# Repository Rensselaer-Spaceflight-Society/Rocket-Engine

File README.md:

# RPU Systems Design and Communications Protocol V1.1.0

> [!IMPORTANT]
> Last Updated: 9/22/2024

Below is a brief overview of the design and communications protocol between our laptop acting as our remote interface (i.e. the control room) and the Rocket Engine Test Stand itself.

## Table of Contents

- [Control Room](#control-room)
- [Test Stand Controller](#test-stand-controller)
- [Powering the Test Stand](#powering-the-test-stand)
- [Sensors](#sensors)
- [Valves](#valves)
- [Communications](#communications)
- [Command and Control](#command-and-control)
- [Sensor Data Transfer](#sensor-data-transfer)
- [Control Flow](#control-flow)
- [Arduino Pinout](#arduino-pinout)
- [Additional Info](#additional-info)

## Control Room

The software that remotely monitors the engine and allows us to send commands to the engine. This software is responsible for:

- Countdown
- Receiving and Saving Data
- Hold and Abort Signals
- Displaying the Data in a Human Friendly Way
  - Charts
  - Text Outputs
  - Color coding for if data is out of spec

### Technologies

We are using C++ and Qt 6.7.2 to build the control room software. You can install the Qt framework for Open Source Usage from https://www.qt.io/download-open-source.

## Test Stand Controller

The rocket engine controller is an Arduino based platform that controls the physical aspects of the rocket engine. This was the primary focus for the semester and is still the primary focus for this summer. This software is responsible for:

- Reading Sensors
- Opening and Closing Valves
- Sending Sensor Data back to the Control Room
- Ignition and Shutoff Sequence
- Processing Control Signals

## Powering the Test Stand

We have a variety of electronics that need power:

- Solenoid Valves, 48W (12vdc @4A)
- Arduino, 1W (12vdc @0.08333)
- Sensors, 5W (5v @1A)

The sensors need 5v, but everything else needs 12v, fortunately, the Arduino's power regulation will step the power down to 5v for the sensors.

Its really hard to send 60w @ 12vdc over 300ft, so we decided that battery power is our best bet for powering the test stand. Lithium Iron Phosphate (LiFePO4) batteries show the best potential for delivering both the voltage and current that the test stand will need.

The use of battery power allows us to set our downrange distance anywhere from 300ft (100m) - 3400ft (1000m).

### Technologies

This is built on the Arduino platform for easy and plentiful I/O. Arduino provides plenty of digital and analog pins for reading sensors and controlling valves. It also provides simple serial communications over UART.

> [!NOTE]
> Originally the rocket engine was supposed to be controlled via Raspberry Pi, we switched to the arduino platform for a couple reasons.
>
> - Setup is easier as there is no need to ssh into the arduino and run the control program, it starts up automatically on power on.
> - The Raspberry Pi has no Analog pin headers, the pressure transducers are analog sensors, switching to Arduino removes the need for analog-digital converters.
> - The Arduino takes less power, we can power it really easily via the VIN and GND pins compared to RasPI which is much harder to power
> - Arduino has first class support for our serial communications, where as raspberry pi has support but is slightly more difficult to implement
> - Arduino has no OS that is also has to run, it just runs our code and our code only.

## Sensors

The rocket engine has 8 sensors:

- 1 Load Cell for measuring thrust
- 4 Thermocouples placed before the injector plate
    - Each one placed at on the injector plate next to the fuel inlets.
- 6 Pressure Transducers
  - 1 Inside the Combustion Chamber
    - According to David, the back of the combustion chamber should be cool enough to not destroy this sensor
  - 1 Down Line of the Inert Gas System
  - 2 Before the injector plate
    - 1 for fuel
    - 1 for oxidizer
  - 2 After the valves for fuel and oxidizer

The pressure transducers are analog sensors that vary their voltage depending on the pressure they are detecting.

The thermocouple and load cell both have amplifiers that act as analog-digital converters. The signals we take in will be digital signals. The thermocouple unfortunately does work on SPI (sorry Ashton).

## Valves

We are using three 12v solenoid valves that operate at 1.33 amps. This is simply too much power to send over a wire with our budget. See the power section for more information.

Power will be delivered to the solenoids via solid-state relays, this allows the
5v logic level of the Arduino power the relays reliably.

## Communications

The goal is to not be anywhere close to the engine when it is firing, the team is still deciding on an acceptable distance, but the current number is between 50 - 100m (170 - 340ft). To achieve this range with easy and reliable communications we are using UART serial communications via ethernet. This provides a well supported, and robust communication method.

> [!IMPORTANT]
> The Baud Rate for the serial communications has yet to be finalized, for testing we are using 9600 but this may change in the future.

Specifically the serial data will be converted to RS485 and sent over Cat 5 ethernet cable, this is supposedly an effective way to handle long range wired communication. [Source](https://electronics.stackexchange.com/questions/113188/long-distance-communication)

The Arduino's serial communication library automatically handles parity, start, and stop bits, so we don't need to handle this necessarily. The default is 8 data, 1 start and 1 stop bit with no parity, but we may be able to change this if needed.

Communications should be handled over the the Serial1 Port on the Arduino, Serial0 (aka just "Serial) is reserved for debugging via the Serial Monitor.

## Command and Control

The control room and the test stand use 64 bit (8 byte) signals to communicate different actions / states to each other the signals are as follows. When the test stand receives a command it should send an acknowledgement. If the control room fails to receive an acknowledgement it should reattempt sending the command up to **5** times. If after these
attempts there still is no acknowledgement, then the control room should assume connection
is lost and notify the user. If the test stand receives a command that it has already received then it should just send an acknowledgement instead of rerunning code.

We are still deciding on what the test stand should do if connection is lost. This document will be updated when this is decided.

The countdown is activated by clicking on the "Start Countdown" button, which will start the countdown from 5 minutes. Once the countdown gets to 30 second, the countdown pauses until you click on the same button that will now read "Resume Countdown". Once you click on it and the countdown reaches 0, it emits a countdown to the main thread where we will begin communication with the rocket. If you click on "Stop Countdown" at any point, the timer will stop at that specific time. Clicking on "Start Countdown" will restart from 5 minutes.

The acknowledgement is an 8 byte sequence:
`Accepted`

The following sequences are the different commands sent by the control computer and what
they tell the test stand to do.

- `CtrlActi` Control Computer Active, tells the test stand that a communication link is active.
- `LogStart` Tells the test stand to start the logging of sensor data and communicating that down the line.
- `InrtFlsh` Tells the test stand to perform an inert gas flush
- `PresFuel` Tells the test stand to open the pressure valve to the Kerosene
- `Ignition` Tells the test stand to open the valves and light the Steel Wool following the ignition protocol
- `Shutdown` Tells the test stand to close the oxidizer valve first, then the fuel valve.

On Shutdown, the test stand should send a message that the engine was shutdown.

## Sensor Data Transfer

Sensor data is sent in packets of 44 bytes of binary data with the following structure:

```cpp
typedef struct
{
  float loadCell;
  float thermocouple[4];
  float pressure[6];
} SensorData;
```

## Control Flow

1. The test stand and the control computer will come online, the control computer will start sending out the signal `CtrlActi` signal. When the test stand receives this, it will send the acknowledgement. On receiving the acknowledgement, the control stand will recognize a connection being solid.
2. The control computer will send the `LogStart` command to tell the test stand to start logging, the test stands sends the acknowledgement, and then will start sending sensor data.
3. At T-10s We will send the `InrtFlsh` command to trigger the test-stand to do the inert flush. 
4. At T-5s We will send the `PresFuel` command to trigger the opening of fuel pressurization valve
5. At T-0.5s We will send the `Ignition` command to initiate the ignition sequence
6. If the test stand detects an anomaly / the end of the test, then it will shutdown and send a message that it shutdown.
7. If the test stand receives the `Shutdown` message, then it should run the shutdown procedure and alert that it shutdown.

## Arduino Pinout

See the Schematic using KiCad for the most up to date Arduino Pins.

## Additional Info

For additional info into how to build the Control Room software, configure the Arduino, and other parts of the project, consult the docs folder of the [GitHub Repository](https://github.com/Rensselaer-Spaceflight-Society/Rocket-Engine)

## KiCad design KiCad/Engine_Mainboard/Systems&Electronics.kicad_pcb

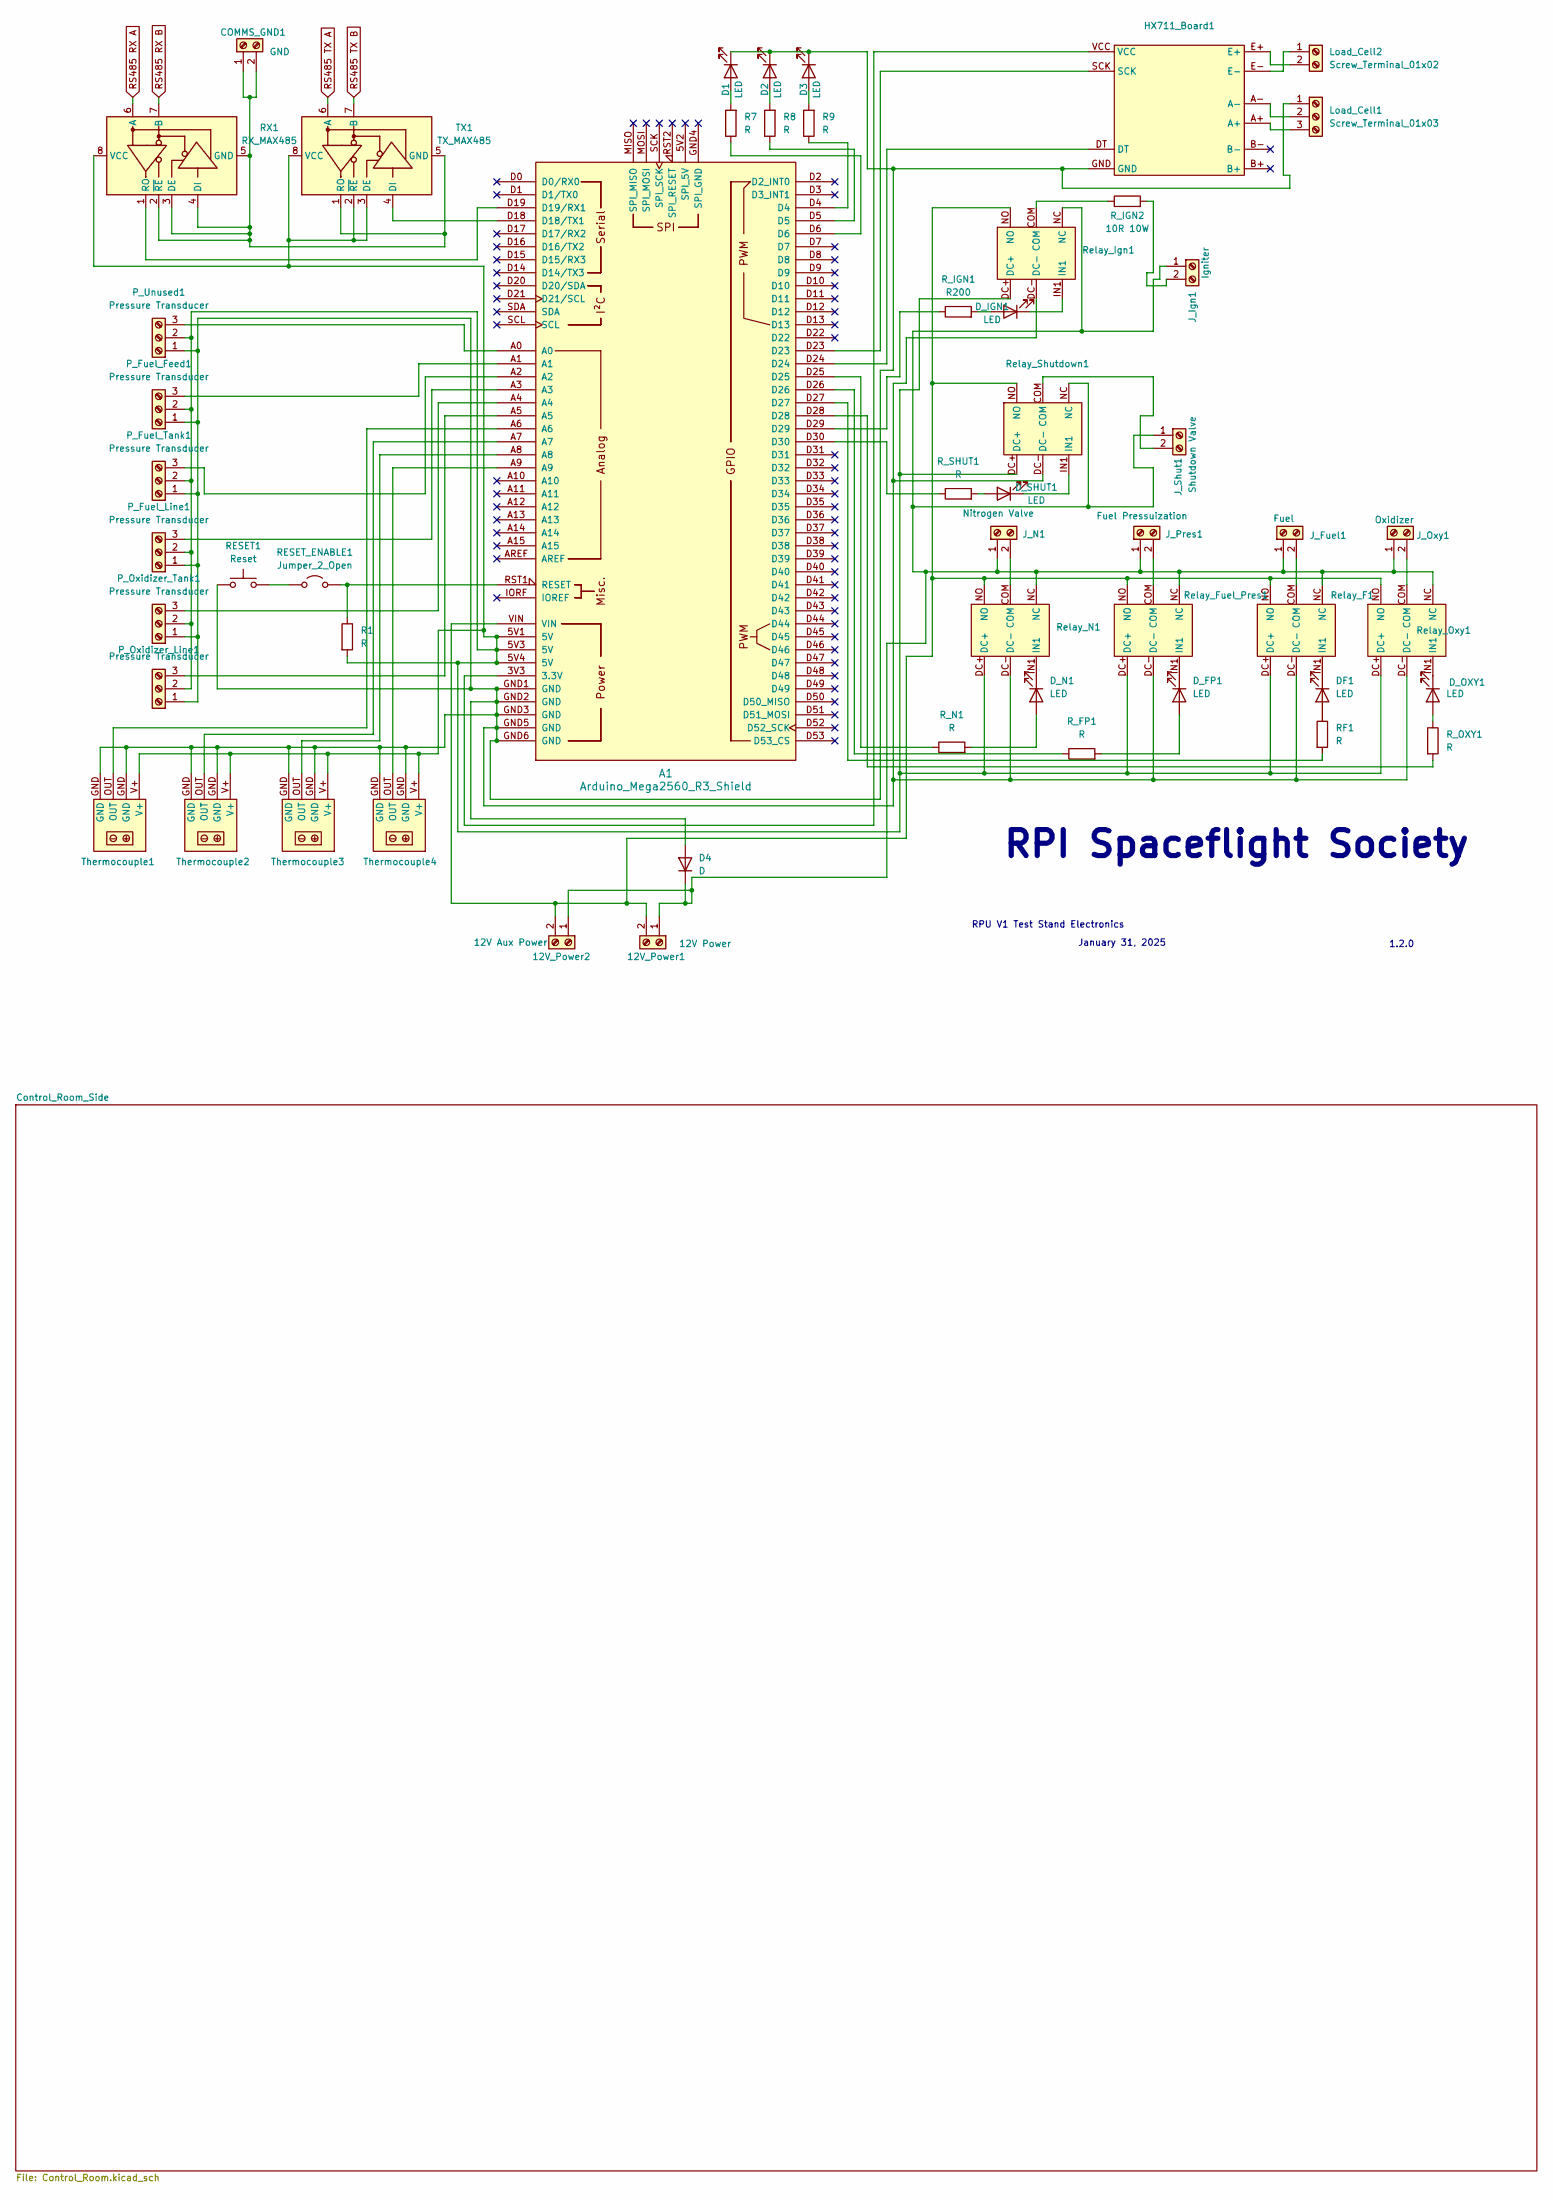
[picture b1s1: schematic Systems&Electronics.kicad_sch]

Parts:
12V_Power1: 12V Power; TerminalBlock_bornier-2_P5.08mm
12V_Power2: 12V Aux Power; TerminalBlock_bornier-2_P5.08mm
A1: Arduino_Mega2560_R3_Shield
COMMS_GND1: GND; TerminalBlock_bornier-2_P5.08mm
D1, D2, D3: LED; LED_D5.0mm
D4: D; D_A-405_P7.62mm_Horizontal
DF1: LED; LED_D5.0mm
D_FP1: LED; LED_D5.0mm
D_IGN1: LED; LED_D5.0mm
D_N1: LED; LED_D5.0mm
D_OXY1: LED; LED_D5.0mm
D_SHUT1: LED; LED_D5.0mm
HX711_Board1: HX711
J_Fuel1: Fuel; TerminalBlock_bornier-2_P5.08mm
J_Ign1: Igniter; TerminalBlock_bornier-2_P5.08mm
J_N1: Nitrogen Valve; TerminalBlock_bornier-2_P5.08mm
J_Oxy1: Oxidizer; TerminalBlock_bornier-2_P5.08mm
J_Pres1: Fuel Pressuization; TerminalBlock_bornier-2_P5.08mm
J_Shut1: Shutdown Valve; TerminalBlock_bornier-2_P5.08mm
Load_Cell1: Screw_Terminal_01x03; TerminalBlock_bornier-3_P5.08mm
Load_Cell2: Screw_Terminal_01x02; TerminalBlock_bornier-2_P5.08mm
P_Fuel_Feed1: Pressure Transducer; TerminalBlock_bornier-3_P5.08mm
P_Fuel_Line1: Pressure Transducer; TerminalBlock_bornier-3_P5.08mm
P_Fuel_Tank1: Pressure Transducer; TerminalBlock_bornier-3_P5.08mm
P_Oxidizer_Line1: Pressure Transducer; TerminalBlock_bornier-3_P5.08mm
P_Oxidizer_Tank1: Pressure Transducer; TerminalBlock_bornier-3_P5.08mm
P_Unused1: Pressure Transducer; TerminalBlock_bornier-3_P5.08mm
R1, R7, R8, R9: R; R_Axial_DIN0207_L6.3mm_D2.5mm_P7.62mm_Horizontal
RESET1: Reset; SW_PUSH_6mm
RESET_ENABLE1: Jumper_2_Open; PinHeader_1x02_P2.54mm_Vertical
RF1: R; R_Axial_DIN0207_L6.3mm_D2.5mm_P7.62mm_Horizontal
RX1: RX_MAX485; RS485_Transceiver
R_FP1: R; R_Axial_DIN0207_L6.3mm_D2.5mm_P7.62mm_Horizontal
R_IGN1: R200; R_Axial_DIN0207_L6.3mm_D2.5mm_P7.62mm_Horizontal
R_IGN2: 10R 10W; R_Axial_Power_L50.0mm_W9.0mm_P55.88mm
R_N1: R; R_Axial_DIN0207_L6.3mm_D2.5mm_P7.62mm_Horizontal
R_OXY1: R; R_Axial_DIN0207_L6.3mm_D2.5mm_P7.62mm_Horizontal
R_SHUT1: R; R_Axial_DIN0207_L6.3mm_D2.5mm_P7.62mm_Horizontal
Relay_F1: Relay
Relay_Fuel_Pres1: Relay
Relay_Ign1: Relay
Relay_N1: Relay
Relay_Oxy1: Relay
Relay_Shutdown1: Relay
TX1: TX_MAX485; RS485_Transceiver
Thermocouple1, Thermocouple2, Thermocouple3, Thermocouple4: AD8495

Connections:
unnamed: 12V_Power1.1, 12V_Power2.1, D4.1 (K), J_Fuel1.1, J_Ign1.1, J_N1.1, J_Oxy1.1, J_Pres1.1, J_Shut1.1, Relay_F1.NC, Relay_Fuel_Pres1.NC, Relay_Ign1.NC, Relay_N1.NC, Relay_Oxy1.NC, Relay_Shutdown1.NC
unnamed: 12V_Power1.2, 12V_Power2.2, A1.VIN, Relay_F1.NO, Relay_Fuel_Pres1.NO, Relay_Ign1.NO, Relay_N1.NO, Relay_Oxy1.NO, Relay_Shutdown1.NO
unnamed: A1.3V3 (3.3V), HX711_Board1.VCC
unnamed: A1.D18 (D18/TX1), TX1.4 (DI)
unnamed: A1.D19 (D19/RX1), RX1.1 (RO)
unnamed: A1.A6, Thermocouple1.OUT
unnamed: A1.A7, Thermocouple2.OUT
unnamed: A1.A8, Thermocouple3.OUT
unnamed: A1.A9, Thermocouple4.OUT
unnamed: A1.D4, R9.1
unnamed: A1.D5, R8.1
unnamed: A1.D6, R7.1
unnamed: A1.D23, HX711_Board1.SCK
unnamed: A1.D24, HX711_Board1.DT
unnamed: A1.D25, R_N1.1
unnamed: A1.D26, R_FP1.1
unnamed: A1.D27, RF1.2
unnamed: A1.D28, R_OXY1.2
unnamed: A1.D29, R_IGN1.1
unnamed: A1.D30, R_SHUT1.1
unnamed: A1.RST1 (RESET), R1.1, RESET_ENABLE1.2 (B)
unnamed: COMMS_GND1.1, COMMS_GND1.2, RX1.2 (~RE), RX1.3 (DE), RX1.4 (DI), RX1.5 (GND), TX1.1 (RO), TX1.5 (GND)
unnamed: D1.2 (A), R7.2
unnamed: A1.GND1 (GND), A1.GND2 (GND), A1.GND3 (GND), A1.GND5 (GND), A1.GND6 (GND), D1.1 (K), D2.1 (K), D3.1 (K), D4.2 (A), HX711_Board1.GND, Load_Cell1.1, P_Fuel_Feed1.1, P_Fuel_Line1.1, P_Fuel_Tank1.1, P_Oxidizer_Line1.1, P_Oxidizer_Tank1.1, P_Unused1.1, RESET1.1, Relay_F1.DC-, Relay_Fuel_Pres1.DC-, Relay_Ign1.DC-, Relay_N1.DC-, Relay_Oxy1.DC-, Relay_Shutdown1.DC-, Thermocouple1.GND, Thermocouple2.GND, Thermocouple3.GND, Thermocouple4.GND
unnamed: D2.2 (A), R8.2
unnamed: D3.2 (A), R9.2
unnamed: DF1.2 (A), RF1.1
unnamed: DF1.1 (K), Relay_F1.IN1
unnamed: D_FP1.2 (A), R_FP1.2
unnamed: D_FP1.1 (K), Relay_Fuel_Pres1.IN1
unnamed: D_IGN1.2 (A), R_IGN1.2
unnamed: D_IGN1.1 (K), Relay_Ign1.IN1
unnamed: D_N1.2 (A), R_N1.2
unnamed: D_N1.1 (K), Relay_N1.IN1
unnamed: D_OXY1.2 (A), R_OXY1.1
unnamed: D_OXY1.1 (K), Relay_Oxy1.IN1
unnamed: D_SHUT1.2 (A), R_SHUT1.2
unnamed: D_SHUT1.1 (K), Relay_Shutdown1.IN1
unnamed: J_Fuel1.2, Relay_F1.COM
unnamed: J_Ign1.2, R_IGN2.2
unnamed: J_N1.2, Relay_N1.COM
unnamed: J_Oxy1.2, Relay_Oxy1.COM
unnamed: J_Pres1.2, Relay_Fuel_Pres1.COM
unnamed: J_Shut1.2, Relay_Shutdown1.COM
unnamed: HX711_Board1.A-, Load_Cell1.2
unnamed: HX711_Board1.A+, Load_Cell1.3
unnamed: HX711_Board1.E-, Load_Cell2.1
unnamed: HX711_Board1.E+, Load_Cell2.2
unnamed: A1.5V1 (5V), A1.5V3 (5V), A1.5V4 (5V), P_Fuel_Feed1.2, P_Fuel_Line1.2, P_Fuel_Tank1.2, P_Oxidizer_Line1.2, P_Oxidizer_Tank1.2, P_Unused1.2, R1.2, RX1.8 (VCC), Relay_F1.DC+, Relay_Fuel_Pres1.DC+, Relay_Ign1.DC+, Relay_N1.DC+, Relay_Oxy1.DC+, Relay_Shutdown1.DC+, TX1.2 (~RE), TX1.3 (DE), TX1.8 (VCC), Thermocouple1.V+, Thermocouple2.V+, Thermocouple3.V+, Thermocouple4.V+
unnamed: A1.A1, P_Fuel_Feed1.3
unnamed: A1.A3, P_Fuel_Line1.3
unnamed: A1.A2, P_Fuel_Tank1.3
unnamed: A1.A5, P_Oxidizer_Line1.3
unnamed: A1.A4, P_Oxidizer_Tank1.3
unnamed: A1.A0, P_Unused1.3
unnamed: RESET1.2, RESET_ENABLE1.1 (A)
unnamed: R_IGN2.1, Relay_Ign1.COM
RS485 RX A: RX1.6 (A)
RS485 RX B: RX1.7 (B)
RS485 TX A: TX1.6 (A)
RS485 TX B: TX1.7 (B)

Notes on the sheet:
RPU V1 Test Stand Electronics
RPI Spaceflight Society
January 31, 2025
1.2.0

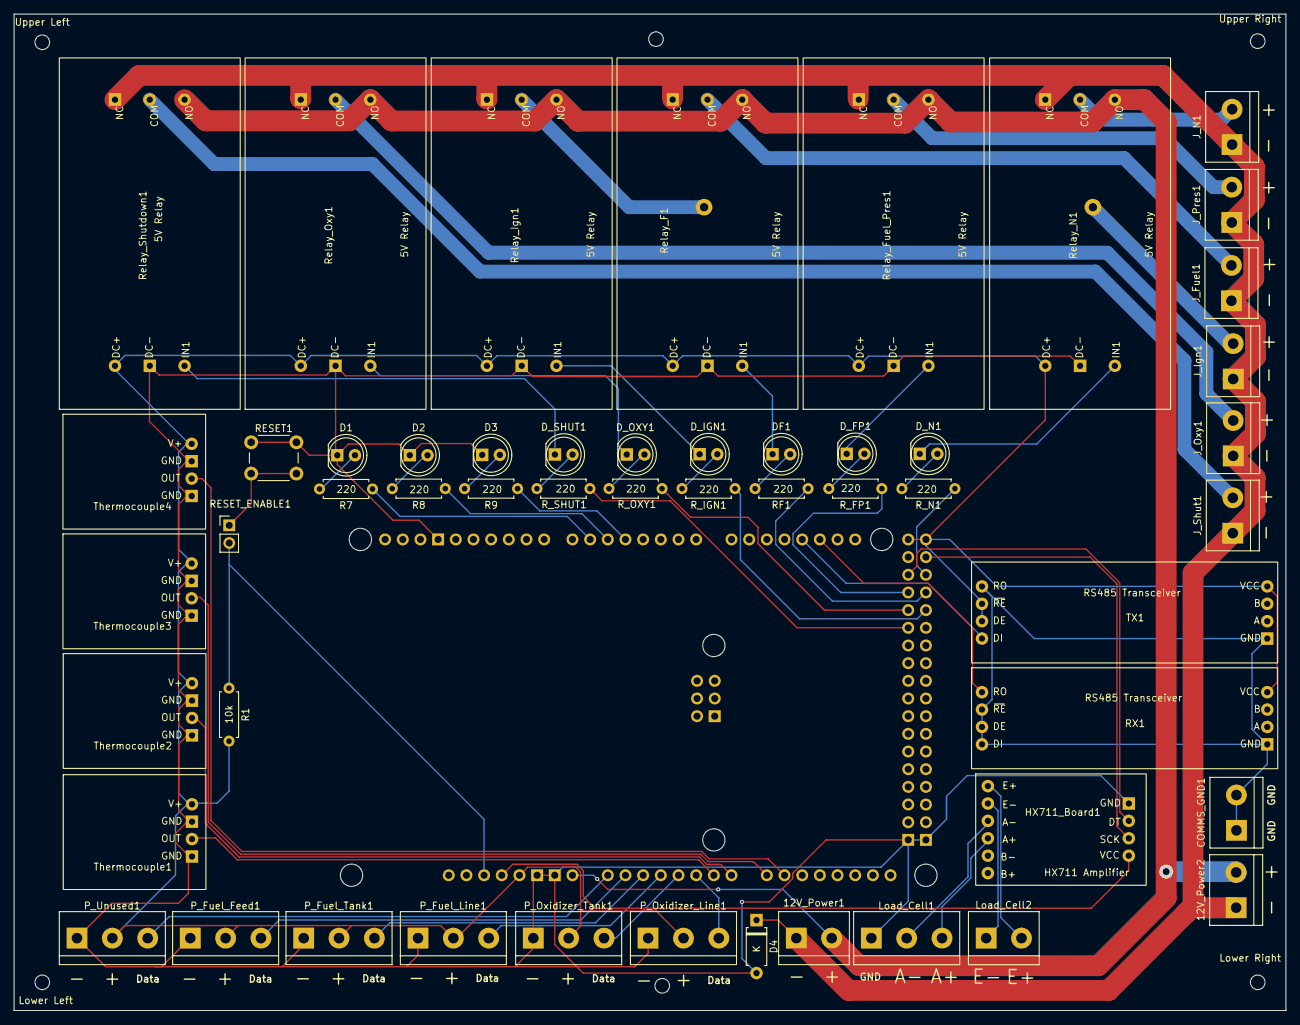
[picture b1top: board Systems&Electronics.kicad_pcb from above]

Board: 2 copper layers, 182.8 x 143.2 mm, 58 parts (1 on the bottom side), 57 nets.

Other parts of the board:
Lower Left: MountingHole_2.1mm
Lower Right: MountingHole_2.1mm
Upper Left: MountingHole_2.1mm
Upper Right: MountingHole_2.1mm

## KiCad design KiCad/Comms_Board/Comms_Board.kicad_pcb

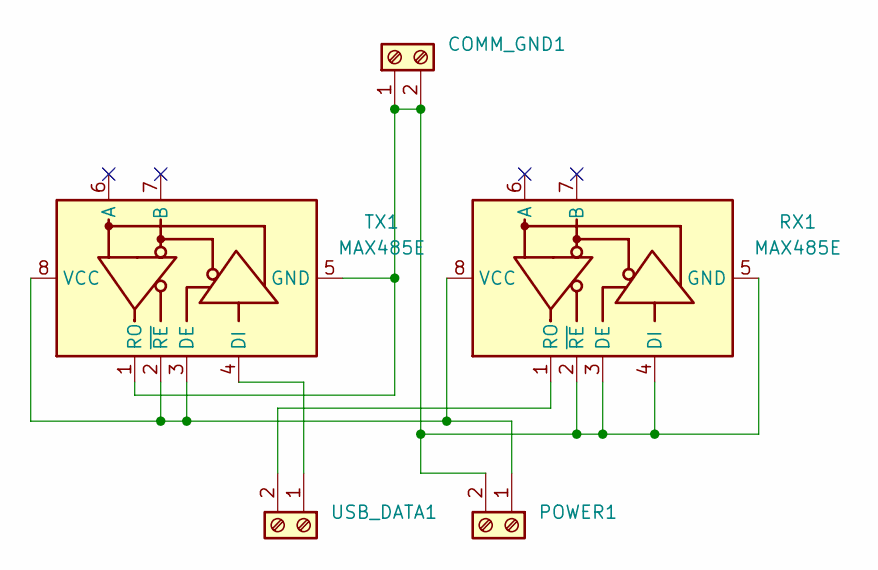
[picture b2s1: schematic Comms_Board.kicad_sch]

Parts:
COMM_GND1: Screw_Terminal_01x02; TerminalBlock_bornier-2_P5.08mm
POWER1: Screw_Terminal_01x02; TerminalBlock_bornier-2_P5.08mm
RX1: MAX485E; RS485_Transceiver
TX1: MAX485E; RS485_Transceiver
USB_DATA1: Screw_Terminal_01x02; TerminalBlock_bornier-2_P5.08mm

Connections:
unnamed: COMM_GND1.1, COMM_GND1.2, POWER1.2, RX1.2 (~RE), RX1.3 (DE), RX1.4 (DI), RX1.5 (GND), TX1.1 (RO), TX1.5 (GND)
unnamed: POWER1.1, RX1.8 (VCC), TX1.2 (~RE), TX1.3 (DE), TX1.8 (VCC)
unnamed: RX1.1 (RO), USB_DATA1.2
unnamed: TX1.4 (DI), USB_DATA1.1

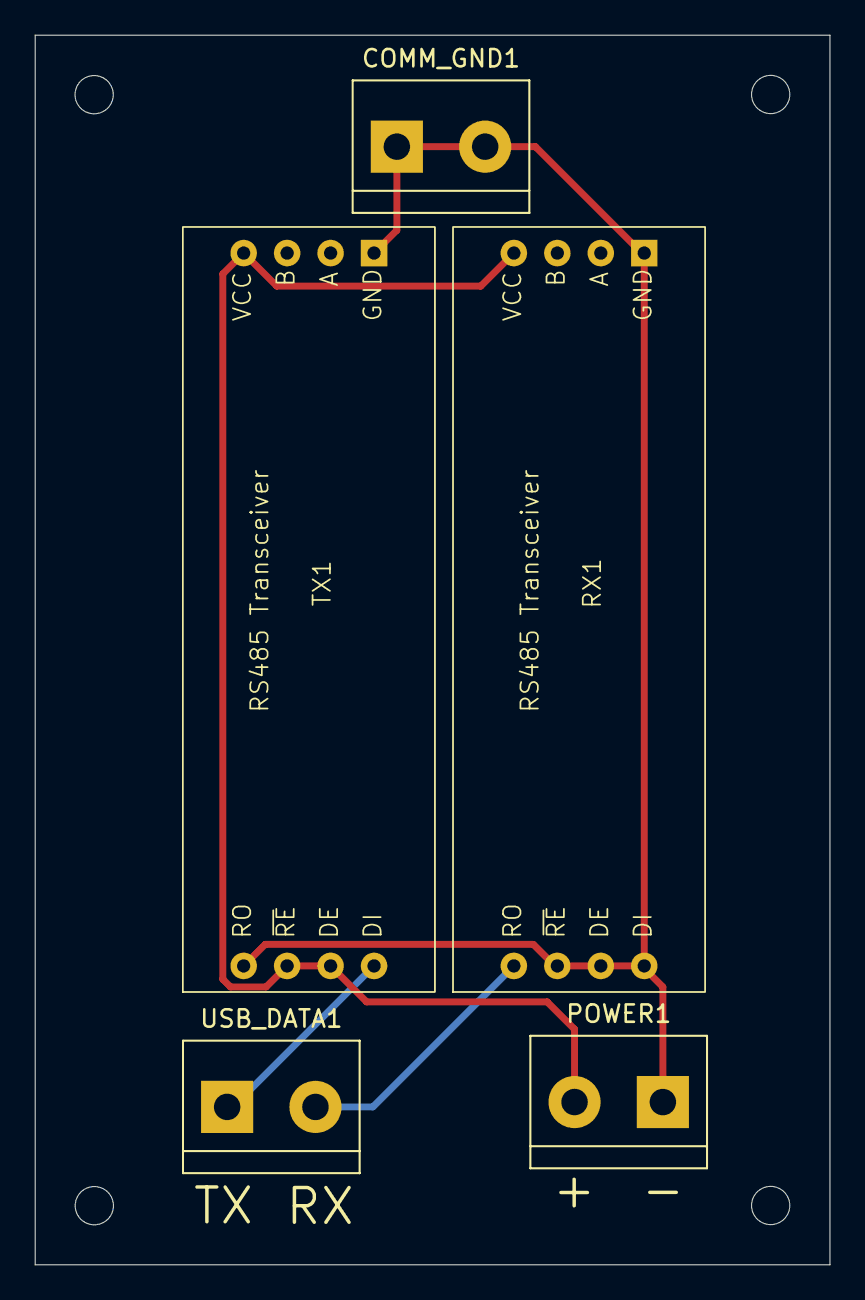
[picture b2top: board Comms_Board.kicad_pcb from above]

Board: 2 copper layers, 45.7 x 70.7 mm, 5 parts (0 on the bottom side), 4 nets.

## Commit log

2023-11-18 adding transmit and receive code
2023-12-02 Adding New Transmission and receive Code
2024-01-14 Update Copyright Ownership
2024-01-14 Scrapping Arduino, Moving to Raspberry Pi, Also Switching to wired comms
2024-01-26 Adding Build System
2024-01-27 build system for the code
2024-02-03 Updating Makefile to work better
2024-02-10 Serial Communicator for Control Room
2024-02-17 Communications First Draft
    - Probably Very Buggy
    - I need hardware to test this
2024-02-17 Adding FTXUI for Control Room UI
2024-02-17 Ok I might need to switch build systems to be able to use FTXUI
2024-02-17 Switching to CMake
2024-02-17 docs for building with CMake
2024-03-16 ftxui is working for control room
2024-03-24 rocket engine UI v1
2024-04-20 migrating to the arduino platform for control
2024-04-20 minor updates to the control code
2024-04-20 Update and Refactor the Engine Control
2024-05-08 Documentation Update
2024-05-08 Updates to Test Stand Controller
    - Much of this needs to be reworked
2024-07-23 Update the Systems Protocols
2024-08-07 Adding unfinished schematics
2024-08-07 V1 Systems Schematics
2024-08-08 Electronics Schematic V1.1.0
2024-08-26 Create engine_control.into (COPY 2)
    This is the second version of the engine_control code - Nhut Lu
2024-08-26 Update engine_control.into (COPY 2)
2024-08-27 Updating the arduino program to match implementation details
2024-09-05 Adding Igniter to Schematic
2024-09-08 updating message receieving protocol
2024-09-08 Starting work on the control room
2024-09-08 implementing feedback
2024-09-10 Adding contributing Guidelines
2024-09-10 Update LICENSE
2024-09-10 chore: add code of conduct
2024-09-10 chore: Bug Report, Feature Request, and PR template
2024-09-11 fix: Adding Resistors, Capacitors, and Diodes to Schematic - Also rerouted 12v ground to not run through the Arduino
2024-09-11 Add the Control Room Side of the Signal Decode
2024-09-11 feat: Add the Control Room Side Signal Decoder
2024-09-12 feat(GUI): Set Up QT Project
2024-09-12 Docs(GUI): Add basic docs to compile and run the Qt program
2024-09-12 chore(GUI): remove old serial comms file
2024-09-15 Testing pressure transducer.
2024-09-22 New rocketControl file
    Remove old engineControl files, and replace with new skeleton code
2024-09-22 Ignition Code Test
    Testing outline of ignition code.
2024-09-22 Update the docs with the new control flow
2024-09-29 Updating the Engine Control 3
    Its updated lmao with functions
2024-09-29 Initial UI Layout
2024-10-04 Adding Charts to the UI
2024-10-05 Add Serial Comm logic
2024-10-05 Added the receive thread and the sending threads.
2024-10-06 feat(GUI): starting coms)
2024-10-06 Added fourth solenoid and associated timer, fixed com lines, added three test LEDs
2024-10-08 feat(GUI): allow for refreshing serial ports
2024-10-08 feat(GUI): backspace triggers abort / shutdown
2024-10-08 project file as well as .cpp files
2024-10-09 Code Cleaning
2024-10-09 Updated Readme\ Basic Logic Changes
    What it says on the Tin
2024-10-13 Thermocouples
    I added thermocouples to the systems schematic.
2024-10-13 Update Systems&Electronics.kicad_sch
    Revised version of the added thermocouples
2024-10-13 Added timer function that updates the command list every 200msec
2024-10-13 Included a basic command queue check
2024-10-13 Updated so that it sends the commands from the command queue
2024-10-13 Basic command class.
2024-10-13 Update test.pro to include the command class
2024-10-15 update gitignore and add testing file
2024-10-15 feat(comms): serial writer implementation v1
2024-10-15 feat(comms): integrate serial writer into main thread
2024-10-16 feat(comms): shutdown logic added
2024-10-16 Changes Requested
    Alright All changes are requested, Press Fuel and Nominal Check still not written because i dont have the data needed for these two functions.
2024-10-20 fix(firmware): minor fixes for thermocouples
2024-10-20 updating docs and adding method to convert analog load cell data to digital
2024-10-20 fix(schematics): remove shorts in pressure transducers
2024-10-20 fixed the 4th solenoid
2024-10-20 add Leds
2024-10-20 Update Schematic to remove unneeded caps and resistors
2024-10-22 Command Writer v2
2024-10-24 feat(comms): data send is partially working
2024-10-25 feat(comms): Serial Command Writer v4 started
2024-10-25 feat(comms): error handling and worker mainloop
2024-10-26 feat(comms): Serial Communications system v4 done
    Needs to be connected to the main file properly
    Needs to be tested
2024-10-27 Countdown
2024-10-27 Arduino code for reading a thermocouple
2024-10-29 feat(GUI): minor fixes
2024-11-01 feat(GUI): starting log handler
2024-11-02 feat(GUI): data and event logger untested
2024-11-03 feat(comms): connecting mainwindow to serial worker
2024-11-04 remove the need for metric data conversion
2024-11-05 Timer now shows minutes, seconds, and millisecs
2024-11-05 has new function that allows pausing timer
2024-11-05 Timer pauses at 30 seconds
2024-11-05 feat(GUI): data logging fix, user alerts, and minor refactor of connections
2024-11-05 fix(GUI): update the names of the chart to adjust for the new sensor placement
2024-11-08 Added section on the countdown
2024-11-09 Included signals
2024-11-12 feat(GUI): UI should update when it receives new data.
    TODO: needs to color the text boxes depending on whether data is in spec
2024-11-12 fix(GUI): fix build and remove extraneous logs
2024-11-15 feat(GUI): first iteration of the engine state machine
2024-11-17 It works
    it works
2024-11-24 Rewriting main to support 1 threaded receiving and sending logic.
2024-11-24 send data
2024-11-24 receiving data
2024-11-24 removed retransmit_bool
2024-11-24 updated retry logic
2024-11-24 Initial loadcell testing code
2024-12-20 updating firmware and schematics to be consistent
2024-12-21 Firmware Refactor (Untested)
2024-12-27 Firmware V1.2 Done
2025-01-02 Implemented FSM for handling engine state.
    TODO:
    - Ability to create new log files when the test is restarted
    - Clearing the graphs when a test is restarted
    - QT Signal and Slot Connections
    - Debugging
2025-01-03 Finished First Implementation
    TODO: Testing, Debugging, and More Testing
2025-01-05 Fixing Window Size
2025-01-06 minor bug fixes
    The arduino is not responding to the commands despite the RX LED
    lighting up.
2025-01-14 Fixing Bugs with Comms
    - Slowly making progress still lots to fix
2025-01-15 Fixed a ton of bugs. Software is getting close to completion.
    - Still need to test data ingest
    - Some of the failsafes seem to not be working quite yet.
2025-01-19 Load Cell Test
    Consistently a Newton Off, but it is non scalling error
2025-01-22 DataChart.cpp is broken :(
    - DataChart is not actually displaying when data is appended to the
    series :(
    - UI probably needs a full refactor
2025-01-22 Revert "DataChart.cpp is broken :("
    This reverts commit a3a053152b76015c90c0f24dfea895c2555afb93.
2025-01-22 DataChart is not Broken :)
    - UI needs a refactor still
2025-01-23 Update chart reset to set the zero point
2025-01-23 Fix a bunch of software and firmware bugs :)
2025-01-26 Add PCB Footprints
2025-01-26 Implemented reading from loadcell
2025-01-31 Adding Relay Footprint
2025-01-31 feat(GUI) Command Reader/Writer Implementation and Starting PCB
    * feat(GUI): starting coms)
    * feat(comms): serial writer implementation v1
    * feat(comms): integrate serial writer into main thread
    * feat(comms): shutdown logic added
    * Command Writer v2
    * feat(comms): data send is partially working
2025-02-02 PCB Layout V1
2025-02-09 PCB layout minor updates
2025-02-09 Footprint and PCB updates
2025-02-10 PCB design reorg
2025-02-10 PCB Ignition Resistor Move
2025-02-10 PCB minor trace move
2025-02-10 feat(PCB): PCB V1.1.0 (#14)
    * PCB Layout V1
    * PCB layout minor updates
    * Footprint and PCB updates
    * PCB design reorg
    * PCB Ignition Resistor Move
    * PCB minor trace move
2025-02-13 Finishing touches, added redundant power terminals, and reset button.
2025-02-13 feat(PCB): update PCB organization, add reset button (#15)
    * Footprint and PCB updates
    * PCB design reorg
    * PCB Ignition Resistor Move
    * PCB minor trace move
    * Finishing touches, added redundant power terminals, and reset button.
2025-02-14 Communications board for RS485
2025-02-16 minor thermocouple shuffle
2025-02-16 trace and hole positioning updates
2025-02-16 feat(PCB): Final PCB Design
2025-05-06 Fixed some communications bugs with commands.
    Fixed shutdown not always working
    Fixed some commands failing to send
2025-05-09 Getting Started with Data Logging
    Graphs are still acting weird and need to be debugged. Making lots of
    progress though!
2025-05-09 Fixed a bug with communication
2025-05-09 Minor communication bug fixes
    Fixed UI Slowdown on higher data rates
2025-05-10 DataChart is working now.
    TODO:
    - Replace Combustion Chamber Chart with Communications Telemetry
    - Test and Test Some More
    - Full integration test once all the hardware is soldered
2025-05-10 Add Communications Telemetry to UI
2025-10-05 Update Startup timings
2025-11-21 Cold-Flow Tested Software
2025-12-18 Arduino Nano Servo Motor Controller
